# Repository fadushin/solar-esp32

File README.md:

This github repository contains [Ki-Cad](https://kicad.org) and other auxiliary files for building a solar charging circuit, designed to charge a Lithium Iron Phosphate (LiFePo4) battery, while the battery powers an ESP32 device.

This circuit is designed to support the following features:

* Over-charge protection, to prevent over-charging of LiFePo4 battery;
* Maximum Power Point Tracking (MPPT), to optimize power extraction from the solar cell;
* Under-voltage protection, to prevent the ESP32 from draining the battery when it cannot deliver sufficient voltage;
* (optional) Charge and charge-done status LEDs;
* (optional) Monitoring of solar cell voltage output;
* (optional) Monitoring of battery voltage;
* (optional) ESP32 LED status pin;
* Small form-factor (1" square)

At the heart of the charging board is a [Consonance CN3801](http://www.consonance-elec.com/pdf/datasheet/DSE-CN3801.pdf), an integrated circuit that uses pulse-width modulation to control a P-channel MOS-FET, providing the appropriate voltage and current to charge a LiFePo4 battery, based on the battery's charge state.  This IC uses the "constant voltage" technique, via a voltage divider on the solar-esp32 charging board to track the maximum power point of the solar panel.  This voltage can be regulated, depending on the solar panel in operation.  (See the [Component Assembly](#component-assembly) section, below, for more information.)

> IMPORTANT.  This circuit is designed for use with Lithium Iron Phosphate (LiFePo4) batteries only.  Do _not_ attempt to use this charging circuit with any other battery chemistry.

With the Ki-Cad files in this repository, you can order a printed circuit board (PCB) at one of your favorite PCB print shops (I use [OshPark](https://oshpark.com)) and get a few copies sent to you for small change.  You will be responsible for procuring and assembling the components on the board (See the [Component Assembly](#component-assembly) section, below).

Using this circuit, I have been able to run an ESP32 indefinitely using a 1500mAh 18650 LiFePo4 battery and a 6V 2W solar panel, with the ESP32 in deep sleep, waking at 1 minute intervals, and briefly connecting to WiFi.  Your mileage may vary, depending your application's power needs.

# License

This work is licensed under the terms of the [BSD License 2.0](https://opensource.org/licenses/BSD-3-Clause).

    Copyright 2021 dushin.net

    Redistribution and use in source and binary forms, with or without modification,
    are permitted provided that the following conditions are met:

      1. Redistributions of source code must retain the above copyright notice,
      this list of conditions and the following disclaimer.

      2. Redistributions in binary form must reproduce the above copyright notice,
      this list of conditions and the following disclaimer in the documentation and/or
      other materials provided with the distribution.

      3. Neither the name of the copyright holder nor the names of its contributors
      may be used to endorse or promote products derived from this software without
      specific prior written permission.

    THIS SOFTWARE IS PROVIDED BY THE COPYRIGHT HOLDERS AND CONTRIBUTORS "AS IS" AND
    ANY EXPRESS OR IMPLIED WARRANTIES, INCLUDING, BUT NOT LIMITED TO, THE IMPLIED
    WARRANTIES OF MERCHANTABILITY AND FITNESS FOR A PARTICULAR PURPOSE ARE DISCLAIMED.
    IN NO EVENT SHALL THE COPYRIGHT HOLDER OR CONTRIBUTORS BE LIABLE FOR ANY DIRECT,
    INDIRECT, INCIDENTAL, SPECIAL, EXEMPLARY, OR CONSEQUENTIAL DAMAGES (INCLUDING, BUT
    NOT LIMITED TO, PROCUREMENT OF SUBSTITUTE GOODS OR SERVICES; LOSS OF USE, DATA, OR
    PROFITS; OR BUSINESS INTERRUPTION) HOWEVER CAUSED AND ON ANY THEORY OF LIABILITY,
    WHETHER IN CONTRACT, STRICT LIABILITY, OR TORT (INCLUDING NEGLIGENCE OR OTHERWISE)
    ARISING IN ANY WAY OUT OF THE USE OF THIS SOFTWARE, EVEN IF ADVISED OF THE
    POSSIBILITY OF SUCH DAMAGE.

# Typical Circuit

The following block diagram illustrates a typical circuit using this charging board (solar-esp32):

               +------------+
               |   solar    |
               |   panel    |
               |            |
               |            |
               |            |
               |    +  -    |
               |    o  o    |
               +----|--|----+
                    |  |
                    |  |
                  +-|--|------------+              +---------------+
                  | o  o            |              |               |
                  | +  -     +3.3v o----------------o +3.3v        |
                  | Solar     vBAT o----------------o IO32 (ex)    |
                  |  in       vSOL o----------------o IO33 (ex)    |
                  |            LED o----------------o IO2 (ex)     |
                  | BAT         EN o----------------o EN           |
                  | +  -       GND o----------------o GND          |
                  | o  o            |              |               |
                  +-|--|------------+              +---------------+
                    |  | solar-esp32                          ESP32
                    |  |
                    |  +-----------------------------+
                    |                                |
                    |   +-------------------------+  |
                    |   |                         |  |
                    +-}| +    LiFePo4 battery   - |{-+
                        |                         |
                        +-------------------------+

The solar-esp32 charging board contains three sets of pins:

* Solar in (+/-)
* BAT (+/-)
* esp32 (+3.3v/vBAT/vSOL/LED/EN/GND)

To use this charging board:

1. Connect the `+` and `-` terminals of the solar cell to the corresponding `Solar in` `+` and `-` pins on the solar-esp32 charging board;
1. Connect the `+` and `-` terminals of the LiFePo4 battery to the corresponding `BAT` `+` and `-` pins on the solar-esp32 charging board;
1. Connect the +3.3v pin of the ESP32 to the corresponding `+3.3v` pin on the solar-esp32 charging board;
1. Connect the GND pin of the ESP32 to the corresponding `GND` pin on the solar-esp32 charging board;
1. Connect the EN (or "chip_pu") pin of the ESP32 to the corresponding `EN` pin on the solar-esp32 charging board.

With this configuration, the ESP32 should run off the LiFePo4 battery, as long as the battery can supply adequate voltage (e.g., 3.2v), and the battery should take a charge from the solar panel as long as the panel can deliver sufficient power to the battery (optimized to the specifications of the solar panel).

See below for more information about the `vSol`, `vBat`, and `LED` pins on the solar-esp32 charging board.

## Optional Voltage Monitoring

The solar-esp32 charging board supports pins for monitoring supply voltage from the solar panel (`vSOL`), as well as supply voltage from the battery (`vBAT`).

The voltage ranges for these pins are provided in the following table:

| solar-esp32 Pin | Voltage range (typical) |
| --- | --- |
| `vSOL` | 0v - 1.5v |
| `vBAT` | 0v - 1.1v |

You may design an application to read these voltage levels using the ADC pins (32-39) on the ESP32, or using an external ADC circuit (e.g., the ADS1115).  Note that if you use the ADC on the ESP32, you should only take readings when the WiFi is inactive.  You should adjust the ADC attenuation based on the voltage ranges of the two pins.

> Note.  Voltage ranges may vary depending on the solar panel and battery in use.

## Optional LED Status

The solar-esp32 charging board contains pads for 3 status LEDs:

* Charging LED (red, typically) -- This LED on when the solar panel is delivering charge to the battery (also blinks when the battery is disconnected and the board is receiving adequate voltage from the solar panel);
* Charing done LED (blue, typically) -- This LED on when the battery is done charging and is no longer delivering current to the battery;
* ESP32 status LED -- This LED is connected to the `LED` pin on the solar-esp32 charging board and can be used by the application to deliver status to the user about the application, using any suitable I/O pin on the ESP32 device.

# Component Assembly

Users are responsible for procurement and assembly of components used on the solar-esp32 charging board.  Most pads are surface mount imperial code 1206 (0.12" x 0.06") and should be readily solderably by hand.  The SOT-23 pads for the MOSFET and voltage supervisor might be a little trickier with a conventional soldering iron, and the 10-pin pad for the CN3801 may be the most challenging.

Many of these components have fixed values that should not need to be adjusted.

The following components, however, may depend on the choice of solar panel, LiFePo4 battery, and attenuation settings for the ADC used to monitor battery voltage.

| Components | Subsystem | Recommended values | Description |
| --- | --- | --- | --- |
| R3, R5 | MPPT voltage divider | 300k, 100k ohms | This set of resistors should set the voltage at the MPPT pin to 1.205v when the solar panel reaches its maximum power point. Recommended values are based on a solar panel MPP of 5.2v, but your solar panel may have a different MPP. Note that the `vSOL` pin is connected to this circuit, so be sure to make any adjustments to ADC attenuation if you are monitoring the solar panel voltage through this pin. |
| R1 | current sense resistor | 0.24 ohms| This resistor sets the current to deliver to the battery when charging in "constant current" mode.  It is a kind of upper-bound on charge current, and is dependent on the battery in service.  The selection of R1 us computed by 120mV/Ic, where Ic is the desired maximum charge current.  The recommended value is based on a ~500mA limit, e.g., for a 1500mAh 18650 LiFePo4 battery.  I have yet to find a small cheap solar panel that can deliver anywhere near this amperage. |
| R7, R9 | battery voltage divider | 226k, 100k ohms | This set of resistors sets the voltage range used to monitor battery voltage.  The recommended values sets the maximum expected voltage (~3.6v) at the `vBAT` pin to 1.1v.  You may adjust these resistors, depending on the attenuation used to read voltage off this pin. |
| U2, C9 | battery voltage supervisor | 3.0v, active-low, 100uF | This voltage supervisor and capacitor is designed to pull the `EN` pin low when battery voltage drops below 3.0v.  When EN is connected to the EN pin on the ESP32, this will disable the ESP32.  You may want to select an active-low voltage supervisor with a different voltage cutoff, depending on your application.  Note that the ESP32 will draw a considerable amount of current when using WiFi, so lower voltage cutoff values tend to work better for applications that make use of WiFi. |

For information about selection of the rest of the components in this charging circuit, please refer to the [CN3801](http://www.consonance-elec.com/pdf/datasheet/DSE-CN3801.pdf) datasheet.

This repository includes a [Bill of Materials](solar-esp32-BOM.csv) that you can use to select components from your favorite parts warehouse.

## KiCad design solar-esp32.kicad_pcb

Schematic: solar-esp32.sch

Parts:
C1, C5: 10uF; CP_Elec_3x6.4
C2, C6, C8: 10uF; C_1206_3216Metric_Pad1.33x1.80mm_HandSolder
C3, C4: 100nF; C_1206_3216Metric_Pad1.33x1.80mm_HandSolder
C7: 220nF; C_1206_3216Metric_Pad1.33x1.80mm_HandSolder
C9: 100uF; C_1206_3216Metric_Pad1.33x1.80mm_HandSolder
D1, D2: D_Schottky; D_1206_3216Metric_Pad1.42x1.75mm_HandSolder
D3, D4, D6: LED; LED_1206_3216Metric_Pad1.42x1.75mm_HandSolder
J1: Solar; PinHeader_1x02_P2.54mm_Vertical
J2: BAT; PinHeader_1x02_P2.54mm_Vertical
J4: ESP32; PinHeader_1x06_P2.54mm_Vertical
L1: L; L-TYA4020
Q1: DMP1045U-7; SOT-23
R1: 0.24; R_1206_3216Metric_Pad1.30x1.75mm_HandSolder
R2, R8: 1k; R_1206_3216Metric_Pad1.30x1.75mm_HandSolder
R3: 300k; R_1206_3216Metric_Pad1.30x1.75mm_HandSolder
R4: 120; R_1206_3216Metric_Pad1.30x1.75mm_HandSolder
R5, R7, R10: 100k; R_1206_3216Metric_Pad1.30x1.75mm_HandSolder
R9: 226k; R_1206_3216Metric_Pad1.30x1.75mm_HandSolder
U1: CN3801
U2: APX803L; SOT-23

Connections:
/ADC: J4.2, R7.2, R9.2
/BAT+: C5.1, C6.1, C8.1, C9.1, J2.2, J4.1, R1.1, R9.1, R10.1, U1.7 (BAT), U2.3
/CHRG: D3.1 (K), U1.3 (~CHRG)
/CHRGLED: D3.2 (A), D4.2 (A), R2.2
/COM: R4.1, U1.5 (COM)
/COM2: C7.1, R4.2
/CSP: L1.2, R1.2, U1.8 (CSP)
/DONE: D4.1 (K), U1.4 (~DONE)
/DRAIN: D1.2 (A), Q1.3 (D)
/DRAIN2: D1.1 (K), D2.1 (K), L1.1
/DRV: Q1.1 (G), U1.10 (DRV)
/EN: J4.5, R10.2, U2.2
/ESP-LED: J4.3, R8.2
/ESP-LED2: D6.2 (A), R8.1
/GND: C1.2, C2.2, C3.2, C5.2, C6.2, C7.2, C8.2, C9.2, D2.2 (A), D6.1 (K), J1.2, J2.1, J4.6, R5.2, R7.1, U1.2 (GND), U2.1
/MPPT: J4.4, R3.2, R5.1, U1.6 (MPPT)
/SOL+: C1.1, C2.1, C3.1, C4.1, J1.1, Q1.2 (S), R2.1, R3.1, U1.9 (VCC)
/VG: C4.2, U1.1 (VG)

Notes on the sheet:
BSD License 2.0

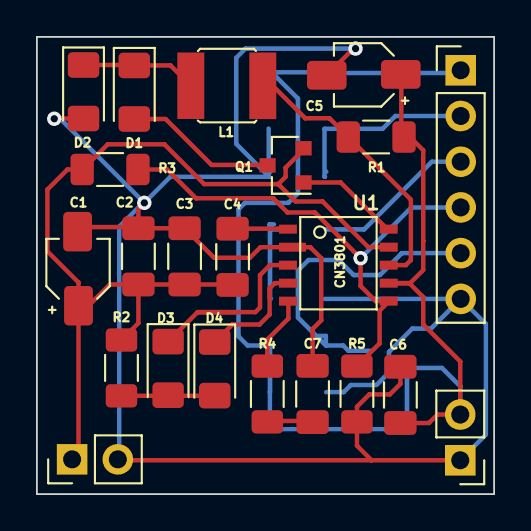
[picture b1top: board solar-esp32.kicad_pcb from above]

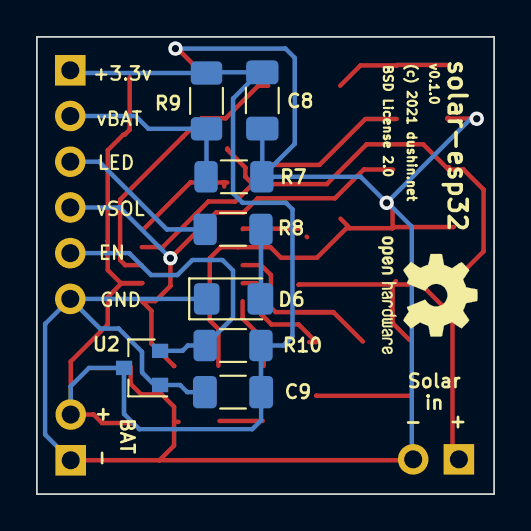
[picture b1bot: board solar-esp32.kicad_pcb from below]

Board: 2 copper layers, 25.4 x 25.4 mm, 30 parts (8 on the bottom side), 18 nets.

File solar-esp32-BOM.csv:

Reference, Value, Footprint, Datasheet
"C1","10uF","0xFD:CP_Elec_3x6.4","https://www.mouser.com/datasheet/2/315/RDE0000C1259-1772497.pdf"
"C2","10uF","Capacitor_SMD:C_1206_3216Metric_Pad1.33x1.80mm_HandSolder","~"
"C3","100nF","Capacitor_SMD:C_1206_3216Metric_Pad1.33x1.80mm_HandSolder","~"
"C4","100nF","Capacitor_SMD:C_1206_3216Metric_Pad1.33x1.80mm_HandSolder","~"
"C5","10uF","0xFD:CP_Elec_3x6.4","https://www.mouser.com/datasheet/2/315/RDE0000C1259-1772497.pdf"
"C6","10uF","Capacitor_SMD:C_1206_3216Metric_Pad1.33x1.80mm_HandSolder","~"
"C7","220nF","Capacitor_SMD:C_1206_3216Metric_Pad1.33x1.80mm_HandSolder","~"
"C8","10uF","Capacitor_SMD:C_1206_3216Metric_Pad1.33x1.80mm_HandSolder","~"
"C9","100uF","Capacitor_SMD:C_1206_3216Metric_Pad1.33x1.80mm_HandSolder","~"
"D1","D_Schottky","Diode_SMD:D_1206_3216Metric_Pad1.42x1.75mm_HandSolder","https://www.mouser.com/datasheet/2/40/schottky-776407.pdf"
"D2","D_Schottky","Diode_SMD:D_1206_3216Metric_Pad1.42x1.75mm_HandSolder","https://www.mouser.com/datasheet/2/40/schottky-776407.pdf"
"D3","LED","LED_SMD:LED_1206_3216Metric_Pad1.42x1.75mm_HandSolder","~"
"D4","LED","LED_SMD:LED_1206_3216Metric_Pad1.42x1.75mm_HandSolder","~"
"D6","LED","LED_SMD:LED_1206_3216Metric_Pad1.42x1.75mm_HandSolder","~"
"J1","Solar","Connector_PinHeader_2.54mm:PinHeader_1x02_P2.54mm_Vertical","~"
"J2","BAT","Connector_PinHeader_2.54mm:PinHeader_1x02_P2.54mm_Vertical","~"
"J4","ESP32","Connector_PinHeader_2.54mm:PinHeader_1x06_P2.54mm_Vertical","~"
"L1","L","0xFD:L-TYA4020","https://www.mouser.com/datasheet/2/987/Laird_Performance_TYA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"
"Q1","DMP1045U-7","Package_TO_SOT_SMD:SOT-23","https://www.mouser.com/datasheet/2/115/DMP1045U-268222.pdf"
"R1","0.24","Resistor_SMD:R_1206_3216Metric_Pad1.30x1.75mm_HandSolder","~"
"R10","100k","Resistor_SMD:R_1206_3216Metric_Pad1.30x1.75mm_HandSolder","~"
"R2","1k","Resistor_SMD:R_1206_3216Metric_Pad1.30x1.75mm_HandSolder","~"
"R3","300k","Resistor_SMD:R_1206_3216Metric_Pad1.30x1.75mm_HandSolder","~"
"R4","120","Resistor_SMD:R_1206_3216Metric_Pad1.30x1.75mm_HandSolder","~"
"R5","100k","Resistor_SMD:R_1206_3216Metric_Pad1.30x1.75mm_HandSolder","~"
"R7","100k","Resistor_SMD:R_1206_3216Metric_Pad1.30x1.75mm_HandSolder","~"
"R8","1k","Resistor_SMD:R_1206_3216Metric_Pad1.30x1.75mm_HandSolder","~"
"R9","226k","Resistor_SMD:R_1206_3216Metric_Pad1.30x1.75mm_HandSolder","~"
"U1","CN3801","0xFD:CN3801","http://www.consonance-elec.com/pdf/datasheet/DSE-CN3801.pdf"
"U2","APX803L","Package_TO_SOT_SMD:SOT-23","https://www.mouser.com/datasheet/2/115/APX803L-1113564.pdf"

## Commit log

2021-02-03 Cleanup
2021-02-04 More cleanup
2021-02-07 Added Zener diode and resistor for low voltage cutoff
2021-02-07 Updated annotations
2021-02-12 improvements and optimizations
2021-02-13 no message
2021-02-21 Improvements
2021-03-20 Made some footprints larger for easier soldering experience.
2021-04-03 Fixed zener diode pad
2021-04-11 Replaced active-high supervisor and p-channel mosfet with an active-low supervisor connected to EN (enable) pin on ESP32.
2021-04-18 Changed to BSD 2.0 license, and added OpenHardware logo
2021-04-18 Added 100uF capacitor near active-low supervisor.
2021-05-03 Enlarged labels on b.silkscreen and updated README.

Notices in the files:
solar-esp32.kicad_pcb:
(c) 2021 dushin.net
